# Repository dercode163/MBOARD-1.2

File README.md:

# MBOARD-1.2
# MBOARD

MBOARD is a compact 9-key macropad powered by an RP2040 microcontroller perfect for custom shortcuts,creative input controls.

# schematic

# CASE

# PCB

#  Features

- 9 programmable keys 
- RP2040 MCU 
- Easy to customize firmware and layout  

# Bill of Materials (BOM)
List of all components used in this project:

| Part | Quantity | Description | 
|------|----------|-------------|
| Mechanical Key Switches | 9 | MX-style switches |
| Keycaps | 9 | Compatible with MX switches | 
| RP2040 Microcontroller | 1 | e.g., Seeed XIAO RP2040 | 
| Custom PCB | 1 | m board Design | 
| 3D Printed Case | 1 | Base + Cover + Top plate |

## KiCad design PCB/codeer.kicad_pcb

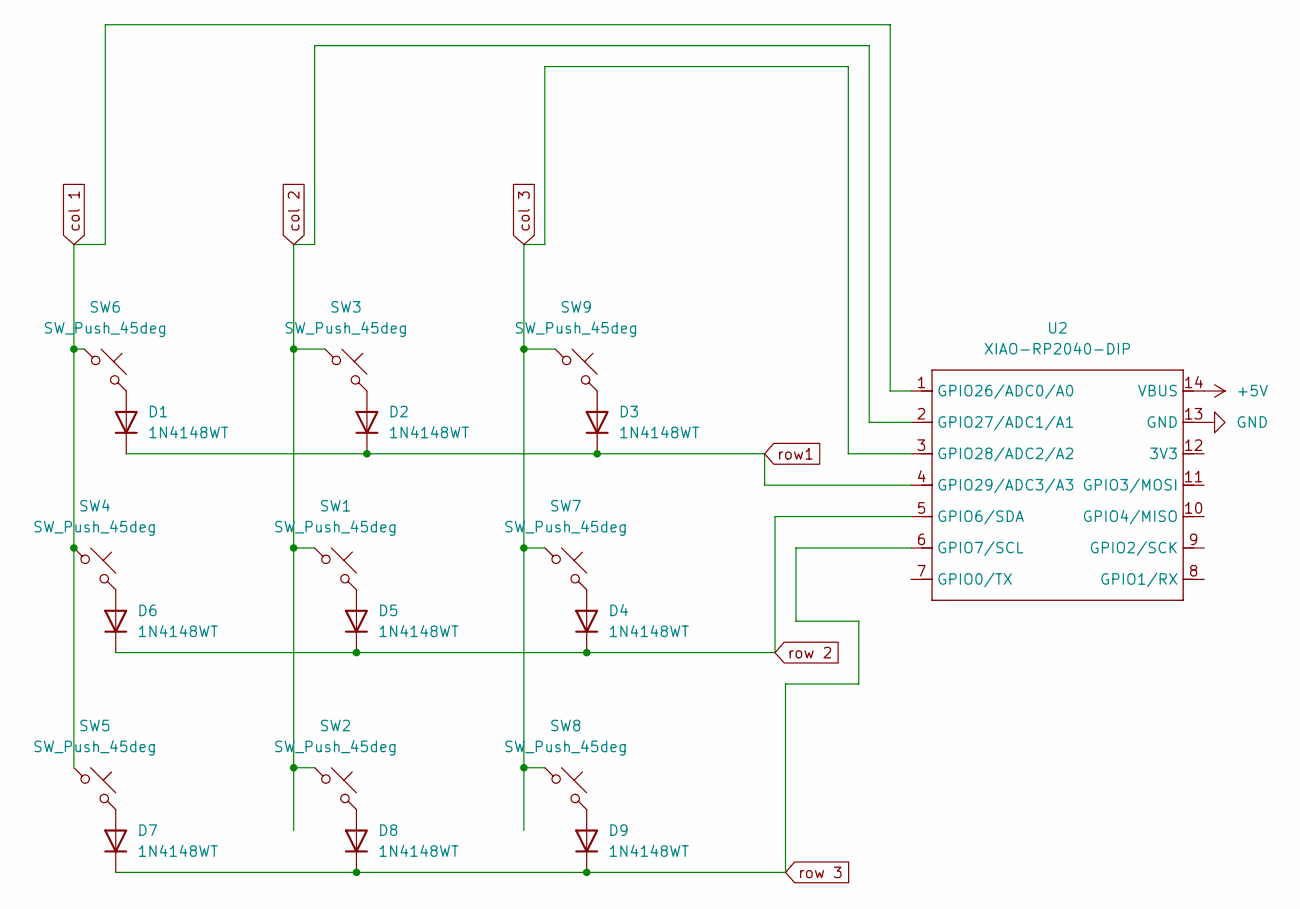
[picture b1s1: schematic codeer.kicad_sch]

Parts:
D1, D2, D3, D4, D5, D6, D7, D8, D9: 1N4148WT; D_SOD-523
SW1, SW2, SW3, SW4, SW5, SW6, SW7, SW8, SW9: SW_Push_45deg
U2: XIAO-RP2040-DIP

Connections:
+5V: U2.14 (VBUS)
GND: U2.13 (GND)
unnamed: D1.2 (A), SW6.2
unnamed: D2.2 (A), SW3.2
unnamed: D3.2 (A), SW9.2
unnamed: D4.2 (A), SW7.2
unnamed: D5.2 (A), SW1.2
unnamed: D6.2 (A), SW4.2
unnamed: D7.2 (A), SW5.2
unnamed: D8.2 (A), SW2.2
unnamed: D9.2 (A), SW8.2
col 1: SW4.1, SW5.1, SW6.1, U2.1 (GPIO26/ADC0/A0)
col 2: SW1.1, SW2.1, SW3.1, U2.2 (GPIO27/ADC1/A1)
col 3: SW7.1, SW8.1, SW9.1, U2.3 (GPIO28/ADC2/A2)
row1: D1.1 (K), D2.1 (K), D3.1 (K), U2.4 (GPIO29/ADC3/A3)
row 2: D4.1 (K), D5.1 (K), D6.1 (K), U2.5 (GPIO6/SDA)
row 3: D7.1 (K), D8.1 (K), D9.1 (K), U2.6 (GPIO7/SCL)

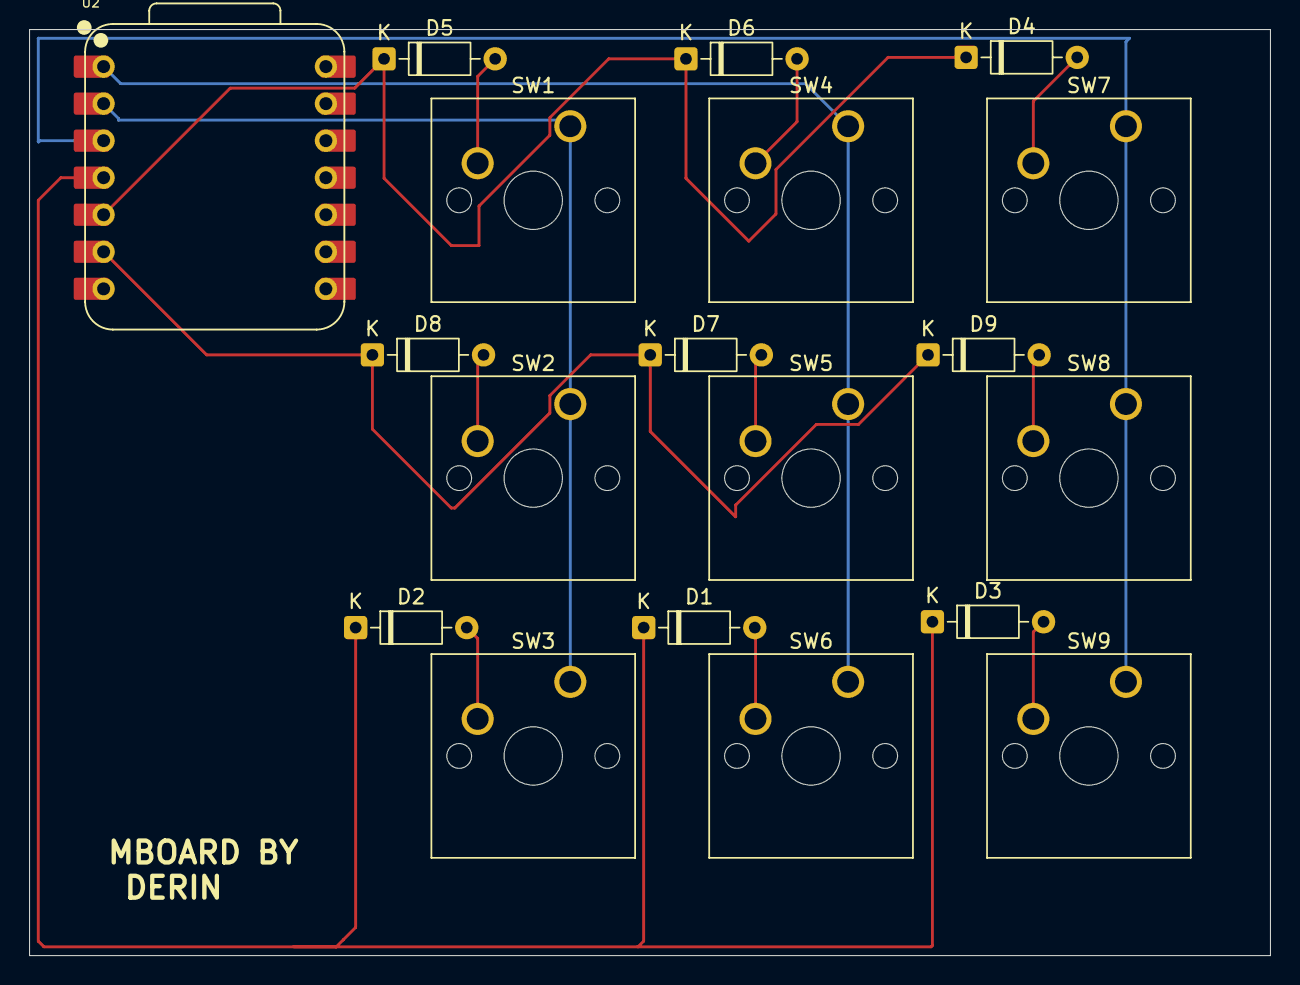
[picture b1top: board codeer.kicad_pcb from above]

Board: 2 copper layers, 85.1 x 63.5 mm, 19 parts (0 on the bottom side), 15 nets.
